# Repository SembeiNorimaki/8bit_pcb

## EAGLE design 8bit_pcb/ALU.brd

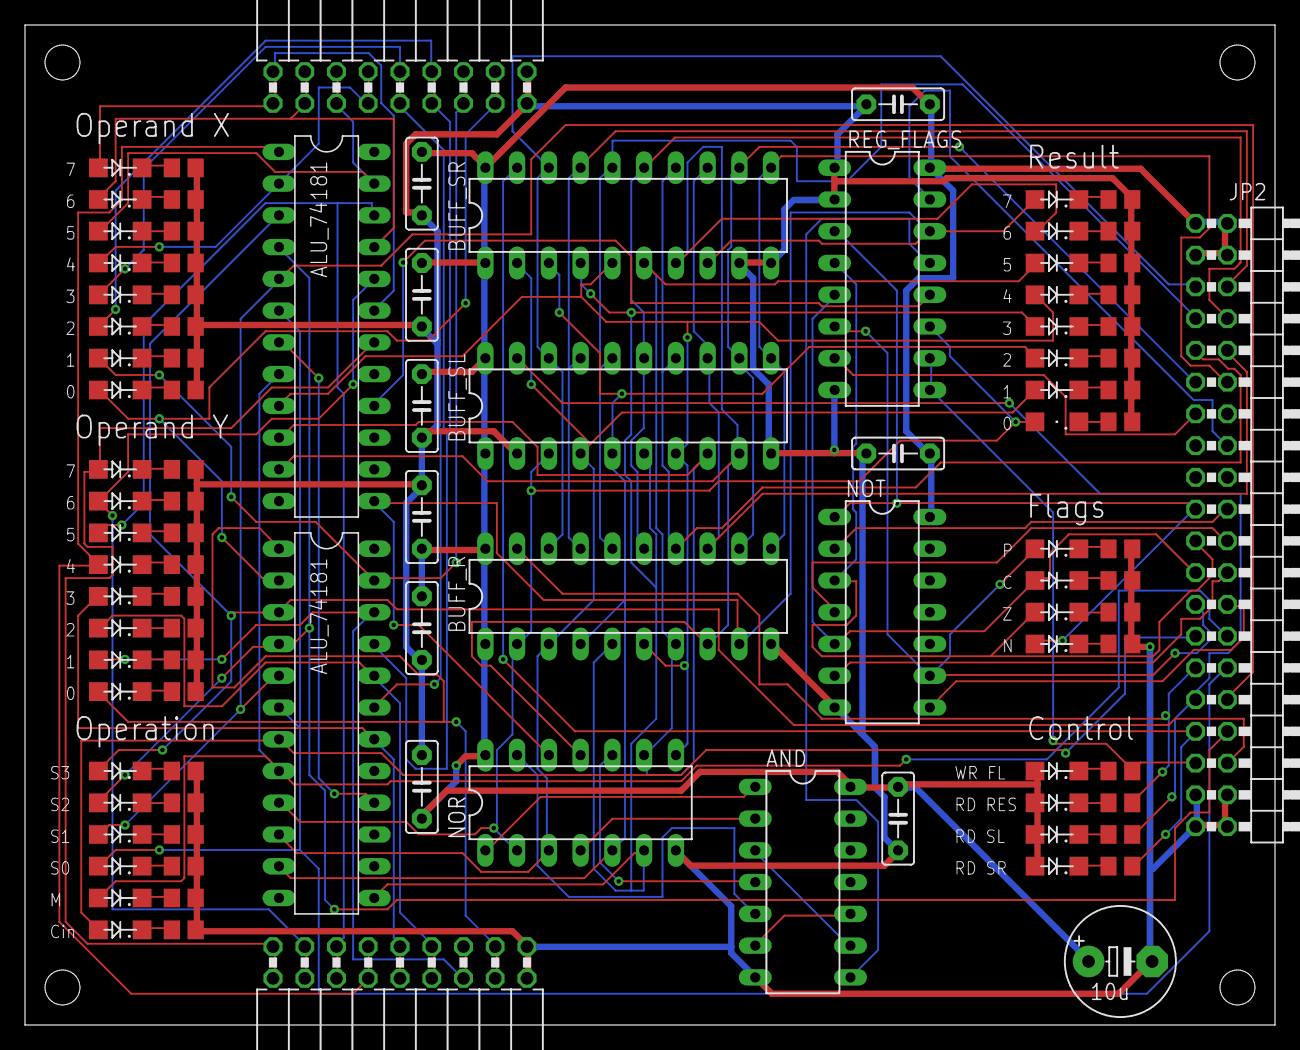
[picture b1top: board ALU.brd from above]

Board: 2 copper layers, 100.0 x 80.0 mm, 98 parts (0 on the bottom side), 101 nets.

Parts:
ALU0, ALU1: ALU_74181
AND: 74LS08N; DIL14
BOTTOM: FE09-2W
BUFF_R: 74LS245N; DIL20
BUFF_SL: 74LS245N; DIL20
BUFF_SR: 74LS245N; DIL20
C1: 10u; E5-8,5
C2, C3, C4, C5, C6, C7, C8, C9, C10: C5B2.5
JP2: 2X20/90
LED1, LED2, LED3, LED4, LED5, LED6, LED7, LED8, LED9, LED10, LED11, LED12, LED13, LED14, LED15, LED16, LED17, LED18, LED19, LED20, LED21, LED22, LED23, LED24, LED25, LED26, LED27, LED28, LED29, LED30, LED31, LED32, LED33, LED34, LED35, LED36, LED37, LED38: SML1206
NOR: 74LS02N; DIL14
NOT: 74LS04N; DIL14
R1, R2, R3, R4, R5, R6, R7, R8, R9, R10, R11, R12, R13, R14, R15, R16, R17, R18, R19, R20, R21, R22, R23, R24, R25, R26, R27, R28, R29, R30, R31, R32, R33, R34, R35, R36, R37, R38: R0805
REG_FLAGS: 74LS173N; DIL16
TOP: FE09-2W

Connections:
!RD_ALU: BUFF_R.19, JP2.29, R35.2
!RD_SL: BUFF_SL.19, JP2.31, R37.2
!RD_SR: BUFF_SR.19, JP2.33, R38.2
!WR_FL: JP2.35, R34.2, REG_FLAGS.9, REG_FLAGS.10
A0: ALU0.A0, LED1.A, TOP.3, TOP.4
A1: ALU0.A1, LED2.A, TOP.5, TOP.6
A2: ALU0.A2, LED3.A, TOP.7, TOP.8
A3: ALU0.A3, LED4.A, TOP.9, TOP.10
A4: ALU1.A0, LED5.A, TOP.11, TOP.12
A5: ALU1.A1, LED6.A, TOP.13, TOP.14
A6: ALU1.A2, LED7.A, TOP.15, TOP.16
A7: ALU1.A3, LED8.A, TOP.17, TOP.18
B0: ALU0.B0, BOTTOM.15, BOTTOM.16, LED9.A
B1: ALU0.B1, BOTTOM.13, BOTTOM.14, LED10.A
B2: ALU0.B2, BOTTOM.11, BOTTOM.12, LED11.A
B3: ALU0.B3, BOTTOM.9, BOTTOM.10, LED12.A
B4: ALU1.B0, BOTTOM.7, BOTTOM.8, LED13.A
B5: ALU1.B1, BOTTOM.5, BOTTOM.6, LED14.A
B6: ALU1.B2, BOTTOM.3, BOTTOM.4, LED15.A
B7: ALU1.B3, BOTTOM.1, BOTTOM.2, LED16.A
BUS0: BUFF_R.18, BUFF_SL.18, BUFF_SR.18, JP2.5
BUS1: BUFF_R.17, BUFF_SL.17, BUFF_SR.17, JP2.6
BUS2: BUFF_R.16, BUFF_SL.16, BUFF_SR.16, JP2.7
BUS3: BUFF_R.15, BUFF_SL.15, BUFF_SR.15, JP2.8
BUS4: BUFF_R.14, BUFF_SL.14, BUFF_SR.14, JP2.9
BUS5: BUFF_R.13, BUFF_SL.13, BUFF_SR.13, JP2.10
BUS6: BUFF_R.12, BUFF_SL.12, BUFF_SR.12, JP2.11
BUS7: BUFF_R.11, BUFF_SL.11, BUFF_SR.11, JP2.12
CIN: ALU0.CN, JP2.27, LED36.A
CLK: JP2.13, REG_FLAGS.7
C_OUT: ALU1.COUT, REG_FLAGS.12
FL_C: JP2.23, LED27.A, NOT.5, REG_FLAGS.5
FL_N: JP2.19, LED25.A, NOT.1, REG_FLAGS.3
FL_P: JP2.25, LED28.A, NOT.9, REG_FLAGS.6
FL_Z: JP2.21, LED26.A, NOT.3, REG_FLAGS.4
GND: AND.7, BOTTOM.17, BOTTOM.18, BUFF_R.10, BUFF_SL.2, BUFF_SL.10, BUFF_SR.9, BUFF_SR.10, C1.-, C2.2, C3.2, C4.2, C5.2, C6.2, C7.2, C8.2, C9.2, C10.2, JP2.37, JP2.38, JP2.39, JP2.40, NOR.7, NOT.7, R1.2, R2.2, R3.2, R4.2, R5.2, R6.2, R7.2, R8.2, R9.2, R10.2, R11.2, R12.2, R13.2, R14.2, R15.2, R16.2, R17.2, R18.2, R19.2, R20.2, R21.2, R22.2, R23.2, R24.2, R25.2, R26.2, R27.2, R28.2, R29.2, R30.2, R31.2, R32.2, R33.2, R36.2, REG_FLAGS.1, REG_FLAGS.2, REG_FLAGS.8, TOP.1, TOP.2
IFL_C: JP2.24, NOT.6
IFL_N: JP2.20, NOT.2
IFL_P: JP2.26, NOT.8
IFL_Z: JP2.22, NOT.4
IRST: JP2.16, REG_FLAGS.15
M: ALU0.M, ALU1.M, JP2.28, LED33.A
unnamed: ALU0.COUT, ALU1.CN
unnamed: AND.1, NOR.1
unnamed: AND.2, NOR.4
unnamed: AND.4, NOR.10
unnamed: AND.5, NOR.13
unnamed: AND.6, AND.10
unnamed: AND.3, AND.9
unnamed: LED29.C, R29.1
unnamed: LED1.C, R1.1
unnamed: LED2.C, R2.1
unnamed: LED3.C, R3.1
unnamed: LED4.C, R4.1
unnamed: LED5.C, R5.1
unnamed: LED6.C, R6.1
unnamed: LED7.C, R7.1
unnamed: LED8.C, R8.1
unnamed: LED30.C, R30.1
unnamed: LED9.C, R9.1
unnamed: LED10.C, R10.1
unnamed: LED11.C, R11.1
unnamed: LED12.C, R12.1
unnamed: LED13.C, R13.1
unnamed: LED14.C, R14.1
unnamed: LED15.C, R15.1
unnamed: LED16.C, R16.1
unnamed: LED31.C, R31.1
unnamed: LED17.C, R17.1
unnamed: LED18.C, R18.1
unnamed: LED19.C, R19.1
unnamed: LED20.C, R20.1
unnamed: LED21.C, R21.1
unnamed: LED22.C, R22.1
unnamed: LED23.C, R23.1
unnamed: LED24.C, R24.1
unnamed: LED25.C, R25.1
unnamed: LED26.C, R26.1
unnamed: LED27.C, R27.1
unnamed: LED28.C, R28.1
unnamed: LED32.C, R32.1
unnamed: LED33.C, R33.1
unnamed: LED34.C, R34.1
unnamed: LED35.C, R35.1
unnamed: LED36.C, R36.1
unnamed: LED37.C, R37.1
unnamed: LED38.C, R38.1
R0: ALU0.F0, BUFF_R.2, BUFF_SL.3, LED17.A, NOR.2, REG_FLAGS.11
R1: ALU0.F1, BUFF_R.3, BUFF_SL.4, BUFF_SR.2, LED18.A, NOR.3
R2: ALU0.F2, BUFF_R.4, BUFF_SL.5, BUFF_SR.3, LED19.A, NOR.5
R3: ALU0.F3, BUFF_R.5, BUFF_SL.6, BUFF_SR.4, LED20.A, NOR.6
R4: ALU1.F0, BUFF_R.6, BUFF_SL.7, BUFF_SR.5, LED21.A, NOR.8
R5: ALU1.F1, BUFF_R.7, BUFF_SL.8, BUFF_SR.6, LED22.A, NOR.9
R6: ALU1.F2, BUFF_R.8, BUFF_SL.9, BUFF_SR.7, LED23.A, NOR.11
R7: ALU1.F3, BUFF_R.9, BUFF_SR.8, LED24.A, NOR.12, REG_FLAGS.14
S0: ALU0.S0, ALU1.S0, JP2.30, LED29.A
S1: ALU0.S1, ALU1.S1, JP2.32, LED30.A
S2: ALU0.S2, ALU1.S2, JP2.34, LED31.A
S3: ALU0.S3, ALU1.S3, JP2.36, LED32.A
VCC: AND.14, BUFF_R.1, BUFF_R.20, BUFF_SL.1, BUFF_SL.20, BUFF_SR.1, BUFF_SR.20, C1.+, C2.1, C3.1, C4.1, C5.1, C6.1, C7.1, C8.1, C9.1, C10.1, JP2.1, JP2.2, JP2.3, JP2.4, LED34.A, LED35.A, LED37.A, LED38.A, NOR.14, NOT.14, REG_FLAGS.16
Z: AND.8, REG_FLAGS.13

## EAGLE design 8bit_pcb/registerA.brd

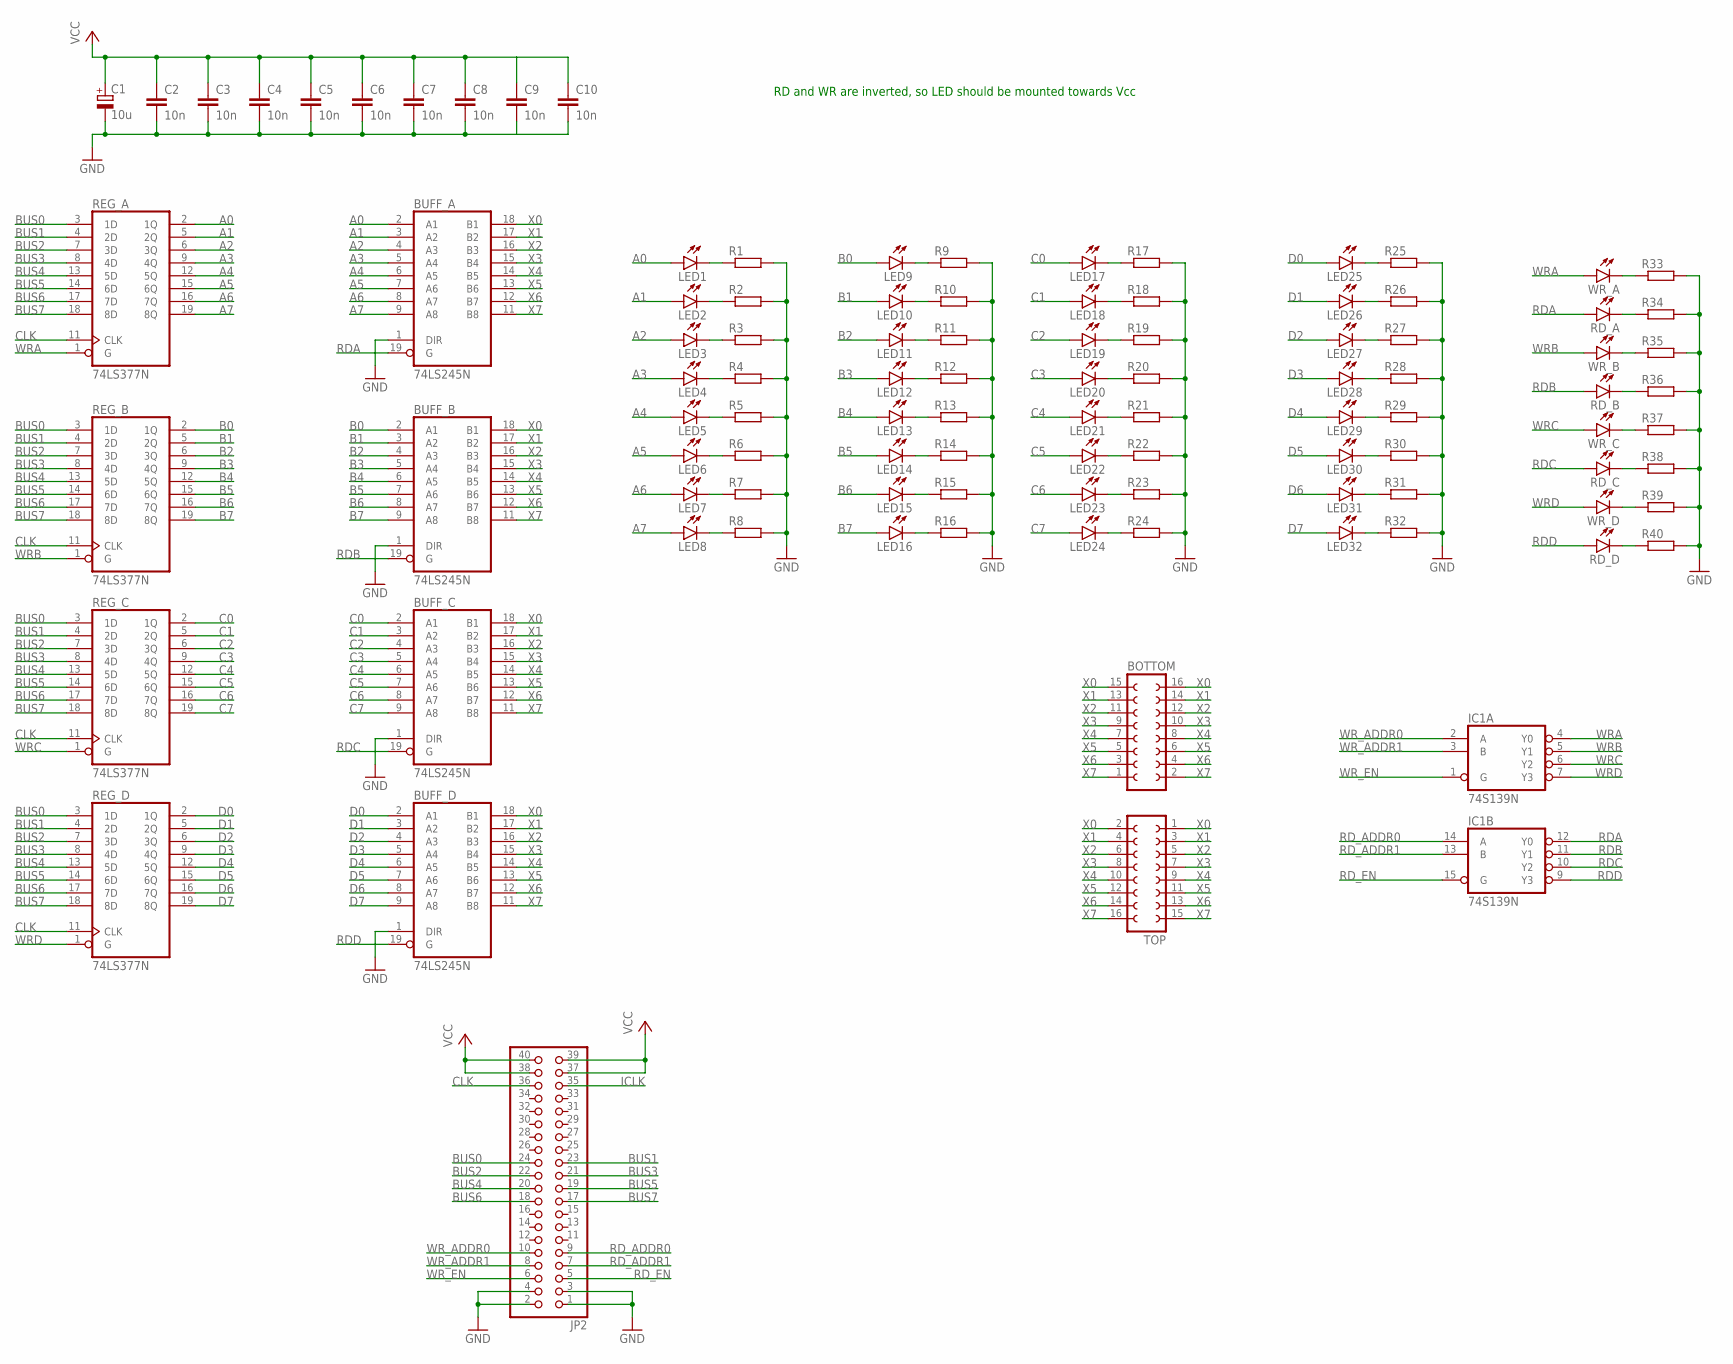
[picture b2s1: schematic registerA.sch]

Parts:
BOTTOM: FE08-2W
BUFF_A: 74LS245N; DIL20
BUFF_B: 74LS245N; DIL20
BUFF_C: 74LS245N; DIL20
BUFF_D: 74LS245N; DIL20
C1: 10u; E5-8,5
C2, C3, C4, C5, C6, C7, C8, C9, C10: 10n; C025-024X044
IC1: 74S139N; DIL16
JP2: PINHD-2X20/90; 2X20/90
LED1, LED2, LED3, LED4, LED5, LED6, LED7, LED8, LED9, LED10, LED11, LED12, LED13, LED14, LED15, LED16, LED17, LED18, LED19, LED20, LED21, LED22, LED23, LED24, LED25, LED26, LED27, LED28, LED29, LED30, LED31, LED32: LEDSML1206; SML1206
R1, R2, R3, R4, R5, R6, R7, R8, R9, R10, R11, R12, R13, R14, R15, R16, R17, R18, R19, R20, R21, R22, R23, R24, R25, R26, R27, R28, R29, R30, R31, R32, R33, R34, R35, R36, R37, R38, R39, R40: R-EU_R0805; R0805
RD_A: LEDSML1206; SML1206
RD_B: LEDSML1206; SML1206
RD_C: LEDSML1206; SML1206
RD_D: LEDSML1206; SML1206
REG_A: 74LS377N; DIL20
REG_B: 74LS377N; DIL20
REG_C: 74LS377N; DIL20
REG_D: 74LS377N; DIL20
TOP: FE08-2W
WR_A: LEDSML1206; SML1206
WR_B: LEDSML1206; SML1206
WR_C: LEDSML1206; SML1206
WR_D: LEDSML1206; SML1206

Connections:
A0: BUFF_A.2 (A1), LED1.A, REG_A.2 (1Q)
A1: BUFF_A.3 (A2), LED2.A, REG_A.5 (2Q)
A2: BUFF_A.4 (A3), LED3.A, REG_A.6 (3Q)
A3: BUFF_A.5 (A4), LED4.A, REG_A.9 (4Q)
A4: BUFF_A.6 (A5), LED5.A, REG_A.12 (5Q)
A5: BUFF_A.7 (A6), LED6.A, REG_A.15 (6Q)
A6: BUFF_A.8 (A7), LED7.A, REG_A.16 (7Q)
A7: BUFF_A.9 (A8), LED8.A, REG_A.19 (8Q)
B0: BUFF_B.2 (A1), LED9.A, REG_B.2 (1Q)
B1: BUFF_B.3 (A2), LED10.A, REG_B.5 (2Q)
B2: BUFF_B.4 (A3), LED11.A, REG_B.6 (3Q)
B3: BUFF_B.5 (A4), LED12.A, REG_B.9 (4Q)
B4: BUFF_B.6 (A5), LED13.A, REG_B.12 (5Q)
B5: BUFF_B.7 (A6), LED14.A, REG_B.15 (6Q)
B6: BUFF_B.8 (A7), LED15.A, REG_B.16 (7Q)
B7: BUFF_B.9 (A8), LED16.A, REG_B.19 (8Q)
BUS0: JP2.24, REG_A.3 (1D), REG_B.3 (1D), REG_C.3 (1D), REG_D.3 (1D)
BUS1: JP2.23, REG_A.4 (2D), REG_B.4 (2D), REG_C.4 (2D), REG_D.4 (2D)
BUS2: JP2.22, REG_A.7 (3D), REG_B.7 (3D), REG_C.7 (3D), REG_D.7 (3D)
BUS3: JP2.21, REG_A.8 (4D), REG_B.8 (4D), REG_C.8 (4D), REG_D.8 (4D)
BUS4: JP2.20, REG_A.13 (5D), REG_B.13 (5D), REG_C.13 (5D), REG_D.13 (5D)
BUS5: JP2.19, REG_A.14 (6D), REG_B.14 (6D), REG_C.14 (6D), REG_D.14 (6D)
BUS6: JP2.18, REG_A.17 (7D), REG_B.17 (7D), REG_C.17 (7D), REG_D.17 (7D)
BUS7: JP2.17, REG_A.18 (8D), REG_B.18 (8D), REG_C.18 (8D), REG_D.18 (8D)
C0: BUFF_C.2 (A1), LED17.A, REG_C.2 (1Q)
C1: BUFF_C.3 (A2), LED18.A, REG_C.5 (2Q)
C2: BUFF_C.4 (A3), LED19.A, REG_C.6 (3Q)
C3: BUFF_C.5 (A4), LED20.A, REG_C.9 (4Q)
C4: BUFF_C.6 (A5), LED21.A, REG_C.12 (5Q)
C5: BUFF_C.7 (A6), LED22.A, REG_C.15 (6Q)
C6: BUFF_C.8 (A7), LED23.A, REG_C.16 (7Q)
C7: BUFF_C.9 (A8), LED24.A, REG_C.19 (8Q)
CLK: JP2.36, REG_A.11 (CLK), REG_B.11 (CLK), REG_C.11 (CLK), REG_D.11 (CLK)
D0: BUFF_D.2 (A1), LED25.A, REG_D.2 (1Q)
D1: BUFF_D.3 (A2), LED26.A, REG_D.5 (2Q)
D2: BUFF_D.4 (A3), LED27.A, REG_D.6 (3Q)
D3: BUFF_D.5 (A4), LED28.A, REG_D.9 (4Q)
D4: BUFF_D.6 (A5), LED29.A, REG_D.12 (5Q)
D5: BUFF_D.7 (A6), LED30.A, REG_D.15 (6Q)
D6: BUFF_D.8 (A7), LED31.A, REG_D.16 (7Q)
D7: BUFF_D.9 (A8), LED32.A, REG_D.19 (8Q)
GND: BUFF_A.1 (DIR), BUFF_A.10 (GND), BUFF_B.1 (DIR), BUFF_B.10 (GND), BUFF_C.1 (DIR), BUFF_C.10 (GND), BUFF_D.1 (DIR), BUFF_D.10 (GND), C1.-, C2.2, C3.2, C4.2, C5.2, C6.2, C7.2, C8.2, C9.2, IC1.8 (GND), JP2.1, JP2.2, JP2.3, JP2.4, R1.2, R2.2, R3.2, R4.2, R5.2, R6.2, R7.2, R8.2, R9.2, R10.2, R11.2, R12.2, R13.2, R14.2, R15.2, R16.2, R17.2, R18.2, R19.2, R20.2, R21.2, R22.2, R23.2, R24.2, R25.2, R26.2, R27.2, R28.2, R29.2, R30.2, R31.2, R32.2, R33.2, R34.2, R35.2, R36.2, R37.2, R38.2, R39.2, R40.2, REG_A.10 (GND), REG_B.10 (GND), REG_C.10 (GND), REG_D.10 (GND)
GND1: C10.2
ICLK: JP2.35
unnamed: LED1.C, R1.1
unnamed: LED2.C, R2.1
unnamed: LED3.C, R3.1
unnamed: LED4.C, R4.1
unnamed: LED5.C, R5.1
unnamed: LED6.C, R6.1
unnamed: LED7.C, R7.1
unnamed: LED8.C, R8.1
unnamed: LED9.C, R9.1
unnamed: LED10.C, R10.1
unnamed: LED11.C, R11.1
unnamed: LED12.C, R12.1
unnamed: LED13.C, R13.1
unnamed: LED14.C, R14.1
unnamed: LED15.C, R15.1
unnamed: LED16.C, R16.1
unnamed: LED17.C, R17.1
unnamed: LED18.C, R18.1
unnamed: LED19.C, R19.1
unnamed: LED20.C, R20.1
unnamed: LED21.C, R21.1
unnamed: LED22.C, R22.1
unnamed: LED23.C, R23.1
unnamed: LED24.C, R24.1
unnamed: LED25.C, R25.1
unnamed: LED26.C, R26.1
unnamed: LED27.C, R27.1
unnamed: LED28.C, R28.1
unnamed: LED29.C, R29.1
unnamed: LED30.C, R30.1
unnamed: LED31.C, R31.1
unnamed: LED32.C, R32.1
unnamed: R33.1, WR_A.C
unnamed: R34.1, RD_A.C
unnamed: R35.1, WR_B.C
unnamed: R36.1, RD_B.C
unnamed: R37.1, WR_C.C
unnamed: R38.1, RD_C.C
unnamed: R39.1, WR_D.C
unnamed: R40.1, RD_D.C
RDA: BUFF_A.19 (G), IC1.12 (Y0), RD_A.A
RDB: BUFF_B.19 (G), IC1.11 (Y1), RD_B.A
RDC: BUFF_C.19 (G), IC1.10 (Y2), RD_C.A
RDD: BUFF_D.19 (G), IC1.9 (Y3), RD_D.A
RD_ADDR0: IC1.14 (A), JP2.9
RD_ADDR1: IC1.13 (B), JP2.7
RD_EN: IC1.15 (G), JP2.5
VCC: BUFF_A.20 (VCC), BUFF_B.20 (VCC), BUFF_C.20 (VCC), BUFF_D.20 (VCC), C1.+, C2.1, C3.1, C4.1, C5.1, C6.1, C7.1, C8.1, C9.1, IC1.16 (VCC), JP2.37, JP2.38, JP2.39, JP2.40, REG_A.20 (VCC), REG_B.20 (VCC), REG_C.20 (VCC), REG_D.20 (VCC)
VCC1: C10.1
WRA: IC1.4 (Y0), REG_A.1 (G), WR_A.A
WRB: IC1.5 (Y1), REG_B.1 (G), WR_B.A
WRC: IC1.6 (Y2), REG_C.1 (G), WR_C.A
WRD: IC1.7 (Y3), REG_D.1 (G), WR_D.A
WR_ADDR0: IC1.2 (A), JP2.10
WR_ADDR1: IC1.3 (B), JP2.8
WR_EN: IC1.1 (G), JP2.6
X0: BOTTOM.15, BOTTOM.16, BUFF_A.18 (B1), BUFF_B.18 (B1), BUFF_C.18 (B1), BUFF_D.18 (B1), TOP.1, TOP.2
X1: BOTTOM.13, BOTTOM.14, BUFF_A.17 (B2), BUFF_B.17 (B2), BUFF_C.17 (B2), BUFF_D.17 (B2), TOP.3, TOP.4
X2: BOTTOM.11, BOTTOM.12, BUFF_A.16 (B3), BUFF_B.16 (B3), BUFF_C.16 (B3), BUFF_D.16 (B3), TOP.5, TOP.6
X3: BOTTOM.9, BOTTOM.10, BUFF_A.15 (B4), BUFF_B.15 (B4), BUFF_C.15 (B4), BUFF_D.15 (B4), TOP.7, TOP.8
X4: BOTTOM.7, BOTTOM.8, BUFF_A.14 (B5), BUFF_B.14 (B5), BUFF_C.14 (B5), BUFF_D.14 (B5), TOP.9, TOP.10
X5: BOTTOM.5, BOTTOM.6, BUFF_A.13 (B6), BUFF_B.13 (B6), BUFF_C.13 (B6), BUFF_D.13 (B6), TOP.11, TOP.12
X6: BOTTOM.3, BOTTOM.4, BUFF_A.12 (B7), BUFF_B.12 (B7), BUFF_C.12 (B7), BUFF_D.12 (B7), TOP.13, TOP.14
X7: BOTTOM.1, BOTTOM.2, BUFF_A.11 (B8), BUFF_B.11 (B8), BUFF_C.11 (B8), BUFF_D.11 (B8), TOP.15, TOP.16

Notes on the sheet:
RD and WR are inverted, so LED should be mounted towards Vcc

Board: 2 copper layers, 102 parts (0 on the bottom side), 105 nets, no tracks yet.

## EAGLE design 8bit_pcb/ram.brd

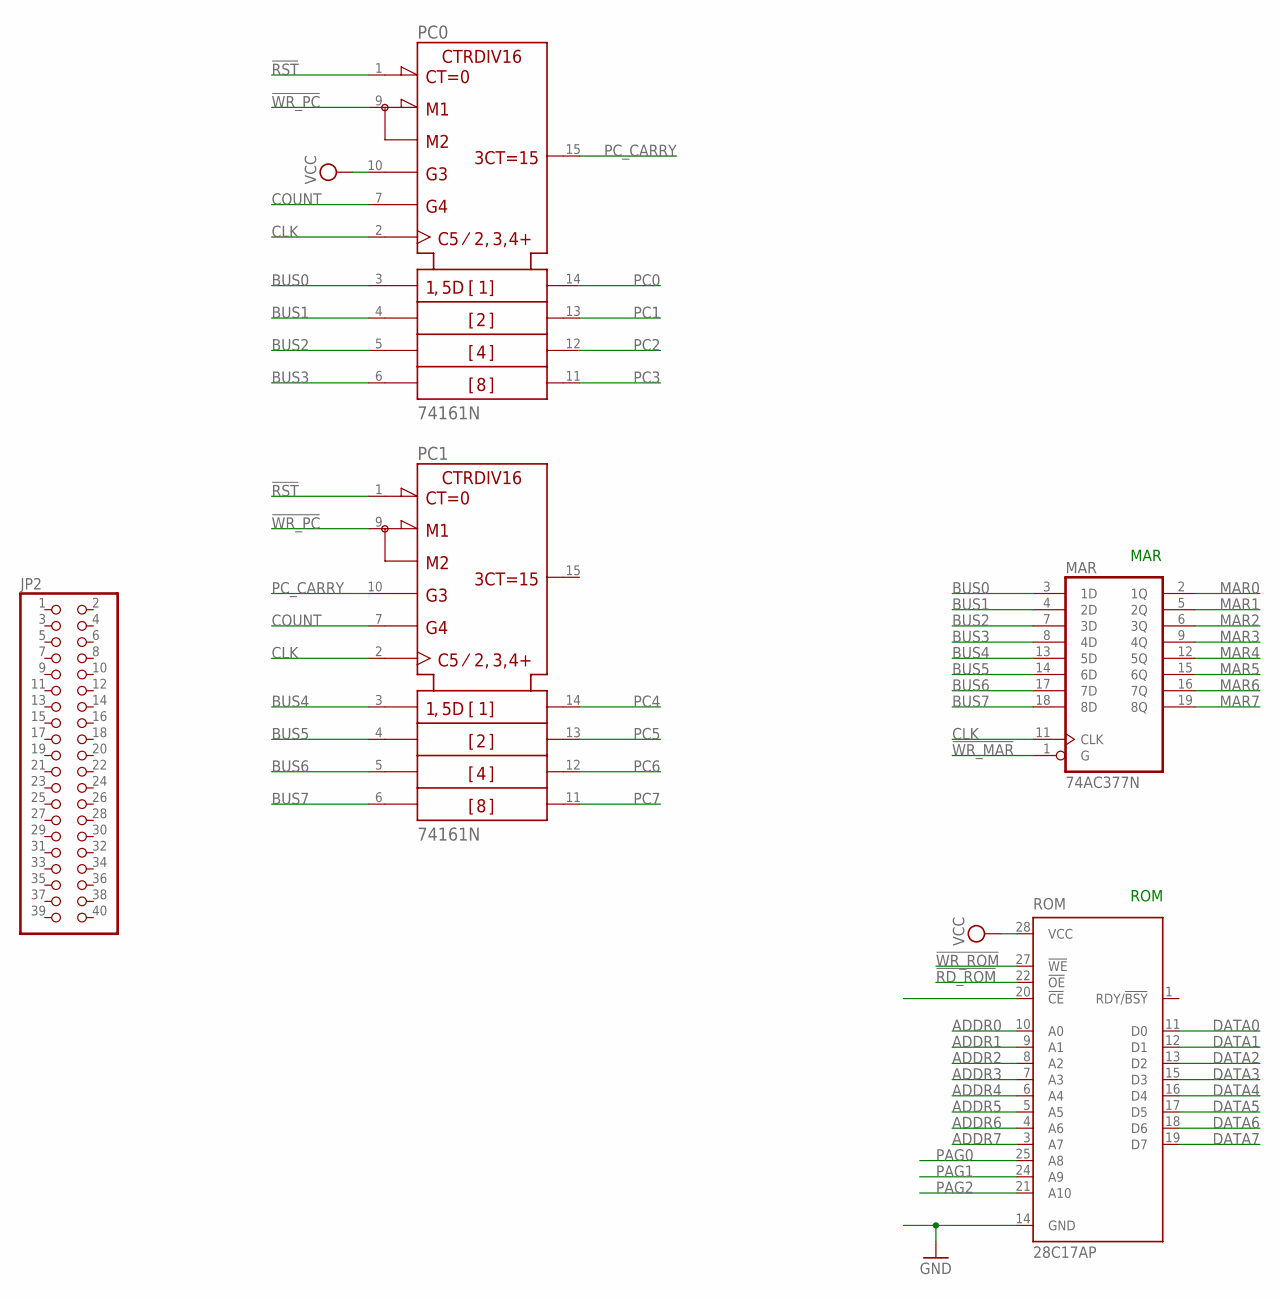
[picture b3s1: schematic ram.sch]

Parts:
JP2: PINHD-2X20/90; 2X20/90
MAR: 74AC377N; DIL20
PC0, PC1: 74161N; DIL16
ROM: 28C17AP; DIL28-6

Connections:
!RD_ROM: ROM.22 (!OE)
!RST: PC0.1 (!CLR), PC1.1 (!CLR)
!WR_MAR: MAR.1 (G)
!WR_PC: PC0.9 (!LOAD), PC1.9 (!LOAD)
!WR_ROM: ROM.27 (!WE)
+UB: PC0.16 (+UB), PC1.16 (+UB)
-UB: PC0.8 (-UB), PC1.8 (-UB)
ADDR0: ROM.10 (A0)
ADDR1: ROM.9 (A1)
ADDR2: ROM.8 (A2)
ADDR3: ROM.7 (A3)
ADDR4: ROM.6 (A4)
ADDR5: ROM.5 (A5)
ADDR6: ROM.4 (A6)
ADDR7: ROM.3 (A7)
BUS0: MAR.3 (1D), PC0.3 (A)
BUS1: MAR.4 (2D), PC0.4 (B)
BUS2: MAR.7 (3D), PC0.5 (C)
BUS3: MAR.8 (4D), PC0.6 (D)
BUS4: MAR.13 (5D), PC1.3 (A)
BUS5: MAR.14 (6D), PC1.4 (B)
BUS6: MAR.17 (7D), PC1.5 (C)
BUS7: MAR.18 (8D), PC1.6 (D)
CLK: MAR.11 (CLK), PC0.2 (CLK), PC1.2 (CLK)
COUNT: PC0.7 (ENP), PC1.7 (ENP)
DATA0: ROM.11 (D0)
DATA1: ROM.12 (D1)
DATA2: ROM.13 (D2)
DATA3: ROM.15 (D3)
DATA4: ROM.16 (D4)
DATA5: ROM.17 (D5)
DATA6: ROM.18 (D6)
DATA7: ROM.19 (D7)
GND: MAR.10 (GND), ROM.14 (GND), ROM.20 (!CE)
MAR0: MAR.2 (1Q)
MAR1: MAR.5 (2Q)
MAR2: MAR.6 (3Q)
MAR3: MAR.9 (4Q)
MAR4: MAR.12 (5Q)
MAR5: MAR.15 (6Q)
MAR6: MAR.16 (7Q)
MAR7: MAR.19 (8Q)
PAG0: ROM.25 (A8)
PAG1: ROM.24 (A9)
PAG2: ROM.21 (A10)
PC0: PC0.14 (QA)
PC1: PC0.13 (QB)
PC2: PC0.12 (QC)
PC3: PC0.11 (QD)
PC4: PC1.14 (QA)
PC5: PC1.13 (QB)
PC6: PC1.12 (QC)
PC7: PC1.11 (QD)
PC_CARRY: PC0.15 (RCO), PC1.10 (ENT)
VCC: MAR.20 (VCC), PC0.10 (ENT), ROM.28 (VCC)

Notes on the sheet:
ROM
MAR

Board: 2 copper layers, 5 parts (0 on the bottom side), 17 nets, no tracks yet.

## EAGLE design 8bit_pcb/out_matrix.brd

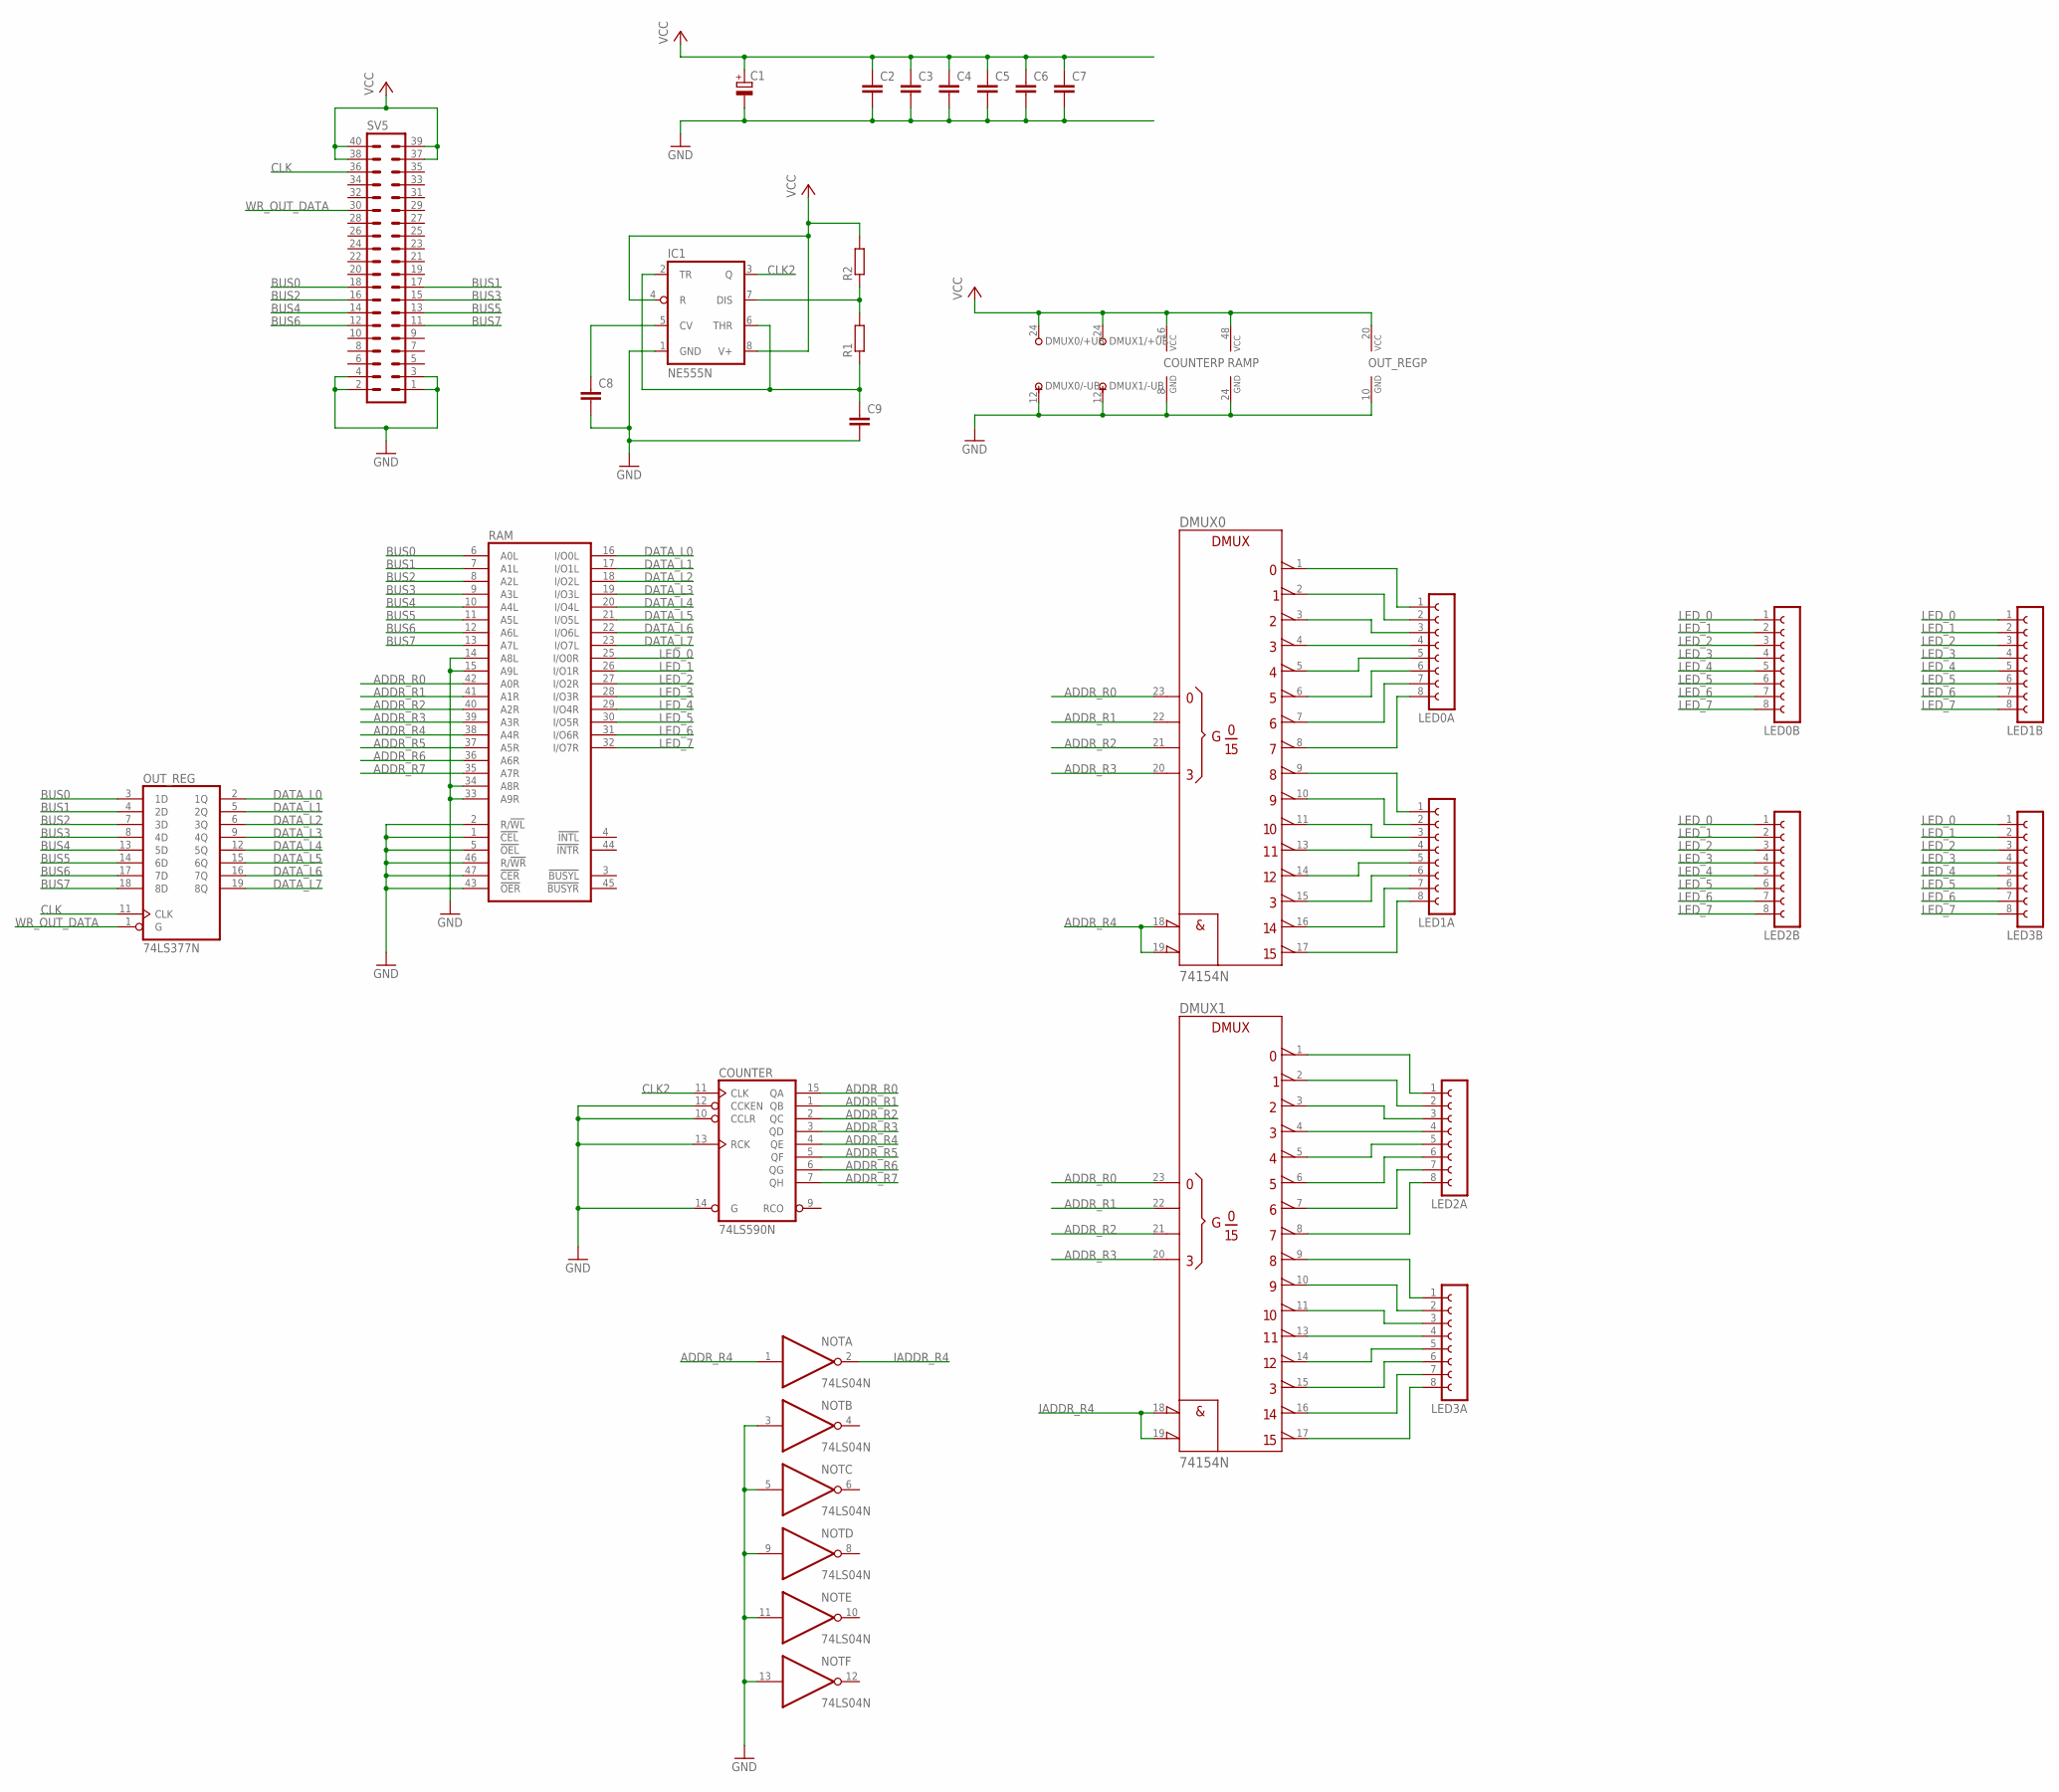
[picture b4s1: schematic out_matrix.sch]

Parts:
C1: CPOL-EUE3.5-8; E3,5-8
C2, C3, C4, C5, C6, C7, C8, C9: C-EUC1206K; C1206K
COUNTER: 74LS590N; DIL16
DMUX0, DMUX1: 74154N; DIL24-3
IC1: NE555N; DIL08
LED0A, LED0B, LED1A, LED1B, LED2A, LED2B, LED3A, LED3B: FE08-1; FE08
NOT: 74LS04N; DIL14
OUT_REG: 74LS377N; DIL20
R1, R2: R-EU_M1206; M1206
RAM: 7130P; DIL48
SV5: MA20-2W

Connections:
ADDR_R0: COUNTER.15 (QA), DMUX0.23 (A), DMUX1.23 (A), RAM.42 (A0R)
ADDR_R1: COUNTER.1 (QB), DMUX0.22 (B), DMUX1.22 (B), RAM.41 (A1R)
ADDR_R2: COUNTER.2 (QC), DMUX0.21 (C), DMUX1.21 (C), RAM.40 (A2R)
ADDR_R3: COUNTER.3 (QD), DMUX0.20 (D), DMUX1.20 (D), RAM.39 (A3R)
ADDR_R4: COUNTER.4 (QE), DMUX0.18 (!G1), DMUX0.19 (!G2), NOT.1 (I), RAM.38 (A4R)
ADDR_R5: COUNTER.5 (QF), RAM.37 (A5R)
ADDR_R6: COUNTER.6 (QG), RAM.36 (A6R)
ADDR_R7: COUNTER.7 (QH), RAM.35 (A7R)
BUS0: OUT_REG.3 (1D), RAM.6 (A0L), SV5.18
BUS1: OUT_REG.4 (2D), RAM.7 (A1L), SV5.17
BUS2: OUT_REG.7 (3D), RAM.8 (A2L), SV5.16
BUS3: OUT_REG.8 (4D), RAM.9 (A3L), SV5.15
BUS4: OUT_REG.13 (5D), RAM.10 (A4L), SV5.14
BUS5: OUT_REG.14 (6D), RAM.11 (A5L), SV5.13
BUS6: OUT_REG.17 (7D), RAM.12 (A6L), SV5.12
BUS7: OUT_REG.18 (8D), RAM.13 (A7L), SV5.11
CLK: OUT_REG.11 (CLK), SV5.36
CLK2: COUNTER.11 (CLK), IC1.3 (Q)
DATA_L0: OUT_REG.2 (1Q), RAM.16 (I/O0L)
DATA_L1: OUT_REG.5 (2Q), RAM.17 (I/O1L)
DATA_L2: OUT_REG.6 (3Q), RAM.18 (I/O2L)
DATA_L3: OUT_REG.9 (4Q), RAM.19 (I/O3L)
DATA_L4: OUT_REG.12 (5Q), RAM.20 (I/O4L)
DATA_L5: OUT_REG.15 (6Q), RAM.21 (I/O5L)
DATA_L6: OUT_REG.16 (7Q), RAM.22 (I/O6L)
DATA_L7: OUT_REG.19 (8Q), RAM.23 (I/O7L)
GND: C1.-, C2.2, C3.2, C4.2, C5.2, C6.2, C7.2, C8.2, C9.2, COUNTER.8 (GND), COUNTER.10 (CCLR), COUNTER.12 (CCKEN), COUNTER.13 (RCK), COUNTER.14 (G), DMUX0.12 (-UB), DMUX1.12 (-UB), IC1.1 (GND), NOT.3 (I), NOT.5 (I), NOT.7 (GND), NOT.9 (I), NOT.11 (I), NOT.13 (I), OUT_REG.10 (GND), RAM.1 (!CEL), RAM.2 (R/!WL), RAM.5 (!OEL), RAM.14 (A8L), RAM.15 (A9L), RAM.24 (GND), RAM.33 (A9R), RAM.34 (A8R), RAM.43 (!OER), RAM.46 (R/!WR), RAM.47 (!CER), SV5.1, SV5.2, SV5.3, SV5.4
IADDR_R4: DMUX1.18 (!G1), DMUX1.19 (!G2), NOT.2 (O)
LED_0: LED0B.1, LED1B.1, LED2B.1, LED3B.1, RAM.25 (I/O0R)
LED_1: LED0B.2, LED1B.2, LED2B.2, LED3B.2, RAM.26 (I/O1R)
LED_2: LED0B.3, LED1B.3, LED2B.3, LED3B.3, RAM.27 (I/O2R)
LED_3: LED0B.4, LED1B.4, LED2B.4, LED3B.4, RAM.28 (I/O3R)
LED_4: LED0B.5, LED1B.5, LED2B.5, LED3B.5, RAM.29 (I/O4R)
LED_5: LED0B.6, LED1B.6, LED2B.6, LED3B.6, RAM.30 (I/O5R)
LED_6: LED0B.7, LED1B.7, LED2B.7, LED3B.7, RAM.31 (I/O6R)
LED_7: LED0B.8, LED1B.8, LED2B.8, LED3B.8, RAM.32 (I/O7R)
unnamed: DMUX1.4 (3), LED2A.4
unnamed: DMUX1.1 (0), LED2A.1
unnamed: DMUX1.2 (1), LED2A.2
unnamed: DMUX1.3 (2), LED2A.3
unnamed: DMUX0.1 (0), LED0A.1
unnamed: DMUX0.2 (1), LED0A.2
unnamed: DMUX0.3 (2), LED0A.3
unnamed: DMUX0.4 (3), LED0A.4
unnamed: DMUX0.8 (7), LED0A.8
unnamed: DMUX0.7 (6), LED0A.7
unnamed: DMUX0.6 (5), LED0A.6
unnamed: DMUX0.5 (4), LED0A.5
unnamed: DMUX0.9 (8), LED1A.1
unnamed: DMUX0.10 (9), LED1A.2
unnamed: DMUX0.11 (10), LED1A.3
unnamed: DMUX0.13 (11), LED1A.4
unnamed: DMUX0.17 (15), LED1A.8
unnamed: DMUX0.16 (14), LED1A.7
unnamed: DMUX0.15 (13), LED1A.6
unnamed: DMUX0.14 (12), LED1A.5
unnamed: DMUX1.8 (7), LED2A.8
unnamed: DMUX1.7 (6), LED2A.7
unnamed: DMUX1.6 (5), LED2A.6
unnamed: DMUX1.5 (4), LED2A.5
unnamed: DMUX1.13 (11), LED3A.4
unnamed: DMUX1.9 (8), LED3A.1
unnamed: DMUX1.10 (9), LED3A.2
unnamed: DMUX1.11 (10), LED3A.3
unnamed: DMUX1.17 (15), LED3A.8
unnamed: DMUX1.16 (14), LED3A.7
unnamed: DMUX1.15 (13), LED3A.6
unnamed: DMUX1.14 (12), LED3A.5
unnamed: IC1.7 (DIS), R1.2, R2.1
unnamed: C8.1, IC1.5 (CV)
unnamed: C9.1, IC1.2 (TR), IC1.6 (THR), R1.1
VCC: C1.+, C2.1, C3.1, C4.1, C5.1, C6.1, C7.1, COUNTER.16 (VCC), DMUX0.24 (+UB), DMUX1.24 (+UB), IC1.4 (R), IC1.8 (V+), NOT.14 (VCC), OUT_REG.20 (VCC), R2.2, RAM.48 (VCC), SV5.37, SV5.38, SV5.39, SV5.40
WR_OUT_DATA: OUT_REG.1 (G), SV5.30

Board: 2 copper layers, 27 parts (0 on the bottom side), 73 nets, no tracks yet.

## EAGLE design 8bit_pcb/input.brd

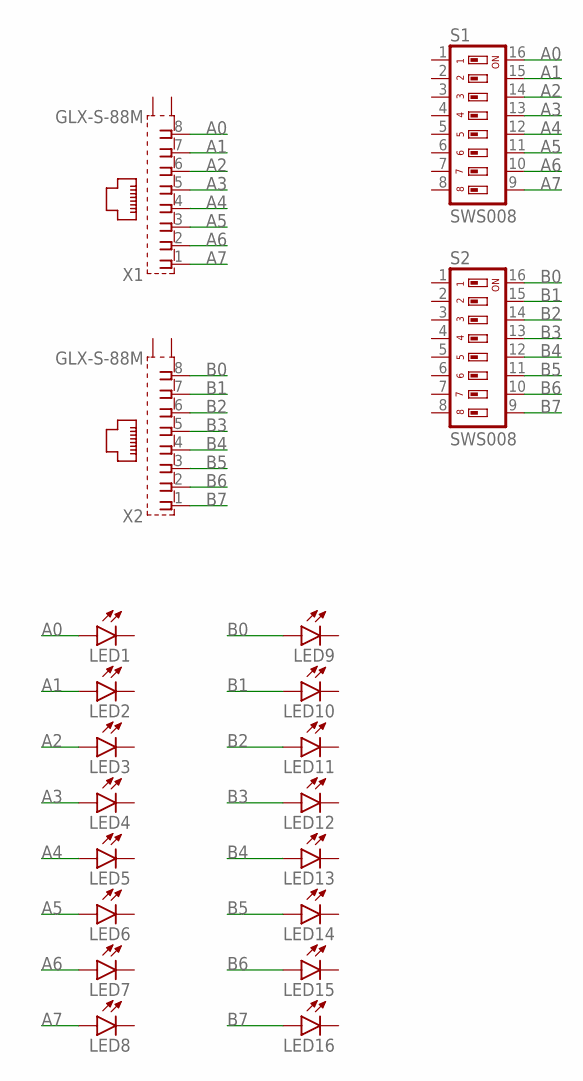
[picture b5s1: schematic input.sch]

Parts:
LED1, LED2, LED3, LED4, LED5, LED6, LED7, LED8, LED9, LED10, LED11, LED12, LED13, LED14, LED15, LED16: LEDSML1206; SML1206
S1, S2: SWS008; SMS-008
X1, X2: GLX-S-88M

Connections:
A0: LED1.A, S1.16, X1.8
A1: LED2.A, S1.15, X1.7
A2: LED3.A, S1.14, X1.6
A3: LED4.A, S1.13, X1.5
A4: LED5.A, S1.12, X1.4
A5: LED6.A, S1.11, X1.3
A6: LED7.A, S1.10, X1.2
A7: LED8.A, S1.9, X1.1
B0: LED9.A, S2.16, X2.8
B1: LED10.A, S2.15, X2.7
B2: LED11.A, S2.14, X2.6
B3: LED12.A, S2.13, X2.5
B4: LED13.A, S2.12, X2.4
B5: LED14.A, S2.11, X2.3
B6: LED15.A, S2.10, X2.2
B7: LED16.A, S2.9, X2.1

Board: 2 copper layers, 20 parts (0 on the bottom side), 16 nets, no tracks yet.

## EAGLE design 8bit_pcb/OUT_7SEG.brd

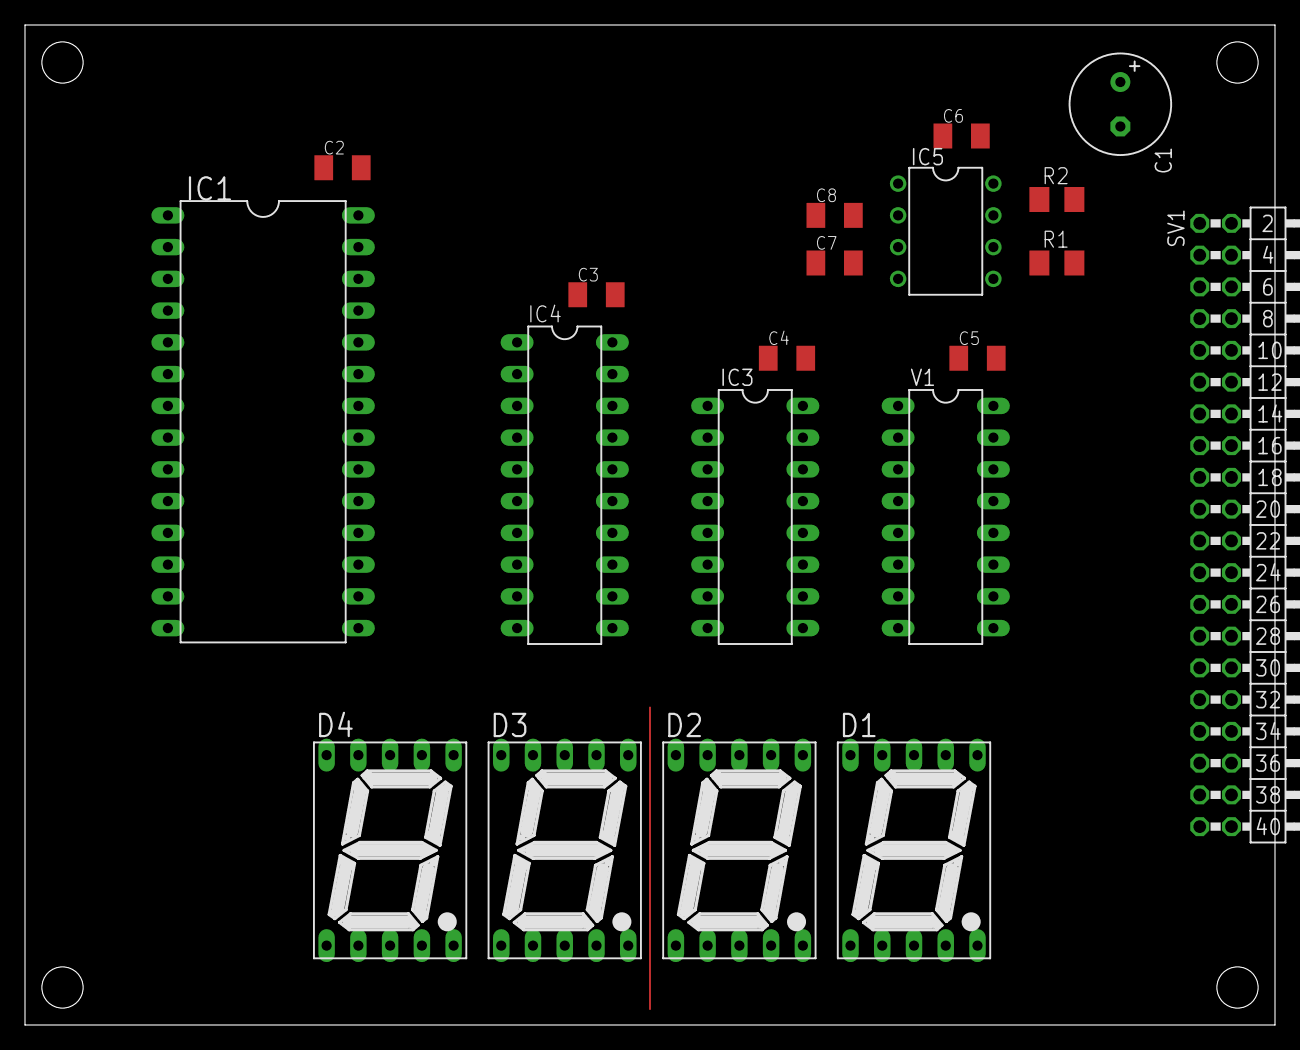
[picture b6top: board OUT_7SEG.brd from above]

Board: 2 copper layers, 100.0 x 80.0 mm, 20 parts (0 on the bottom side), 39 nets.

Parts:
C1: E3,5-8
C2, C3, C4, C5, C6, C7, C8: C1206K
D1, D2, D3, D4: 7SEG-13
IC1: DIL28-6
IC3: 74LS139N; DIL16
IC4: 74LS377N; DIL20
IC5: NE555N; DIL08
R1, R2: M1206
SV1: MA20-2W
V1: 74161N; DIL16

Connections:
ADDR_0: IC1.8, IC4.2
ADDR_1: IC1.7, IC4.5
ADDR_2: IC1.6, IC4.6
ADDR_3: IC1.5, IC4.9
ADDR_4: IC1.4, IC4.12
ADDR_5: IC1.3, IC4.15
ADDR_6: IC1.25, IC4.16
ADDR_7: IC1.24, IC4.19
BUS0: IC4.3, SV1.20
BUS1: IC4.4, SV1.19
BUS2: IC4.7, SV1.18
BUS3: IC4.8, SV1.17
BUS4: IC4.13, SV1.16
BUS5: IC4.14, SV1.15
BUS6: IC4.17, SV1.14
BUS7: IC4.18, SV1.13
CLK: IC4.11, SV1.36
CLK2: IC5.3, V1.2
CNT0: IC1.10, IC3.2, V1.14
CNT1: IC1.9, IC3.3, V1.13
EN0: D1.3, D1.8, IC3.4
EN1: D2.3, D2.8, IC3.5
EN2: D3.3, D3.8, IC3.6
EN3: D4.3, D4.8, IC3.7
GND: C1.-, C2.2, C3.2, C4.2, C5.2, C6.2, C7.2, C8.2, IC1.2, IC1.14, IC1.20, IC1.22, IC1.23, IC3.1, IC3.8, IC4.10, IC5.1, SV1.1, SV1.2, SV1.3, SV1.4, V1.3, V1.4, V1.5, V1.6, V1.8
unnamed: IC5.7, R1.2, R2.1
unnamed: C8.1, IC5.5
unnamed: C7.1, IC5.2, IC5.6, R1.1
NEG: IC1.21, SV1.31
OUT_0: D1.7, D2.7, D3.7, D4.7, IC1.11
OUT_1: D1.6, D2.6, D3.6, D4.6, IC1.12
OUT_2: D1.4, D2.4, D3.4, D4.4, IC1.13
OUT_3: D1.2, D2.2, D3.2, D4.2, IC1.15
OUT_4: D1.1, D2.1, D3.1, D4.1, IC1.16
OUT_5: D1.9, D2.9, D3.9, D4.9, IC1.17
OUT_6: D1.10, D2.10, D3.10, D4.10, IC1.18
OUT_7: D1.5, D2.5, D3.5, D4.5, IC1.19
VCC: C1.+, C2.1, C3.1, C4.1, C5.1, C6.1, IC1.27, IC1.28, IC3.13, IC3.14, IC3.15, IC3.16, IC4.20, IC5.4, IC5.8, R2.2, SV1.37, SV1.38, SV1.39, SV1.40, V1.1, V1.7, V1.9, V1.10, V1.16
WR_OUT: IC4.1, SV1.32

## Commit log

2023-09-24 reg bank and alu finished
2023-09-24 added library
